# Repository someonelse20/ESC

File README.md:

# ESC

A custom designed electronic speed controller that supports up to 7 cell LiPo batteries with 30 amps (untested).
I made this as part of my overall project of making a drone from scratch.

## Pinout

| Pin # | Function  |
| ----- | --------- |
| 1     | PWM IN    |
| 2     | Direction |
| 3     | GND       |

Pull the Direction pin low (default) for clockwise rotation or high (3.3v) for counter clockwise rotation.
Alternatively, leave the solder bridge on the bottom of the board open for clockwise and closed for counter clockwise.

## PCB Layout

## Schematic

## BOM

| Name         | Purpose                   | Quantity | Total Cost (USD) | Link                          | Distributor |
| ------------ | ------------------------- | -------- | ---------------- | ----------------------------- | ----------- |
| PCB          | 	The Circuit Board        | 5        | 7.00             | [JLCPCB](https://jlcpcb.com/) | JLCPCB      |
| PCB Assembly | Assembly for the board    | 2        | 78.46            | [JLCPCB](https://jlcpcb.com/) | JLCPCB      |

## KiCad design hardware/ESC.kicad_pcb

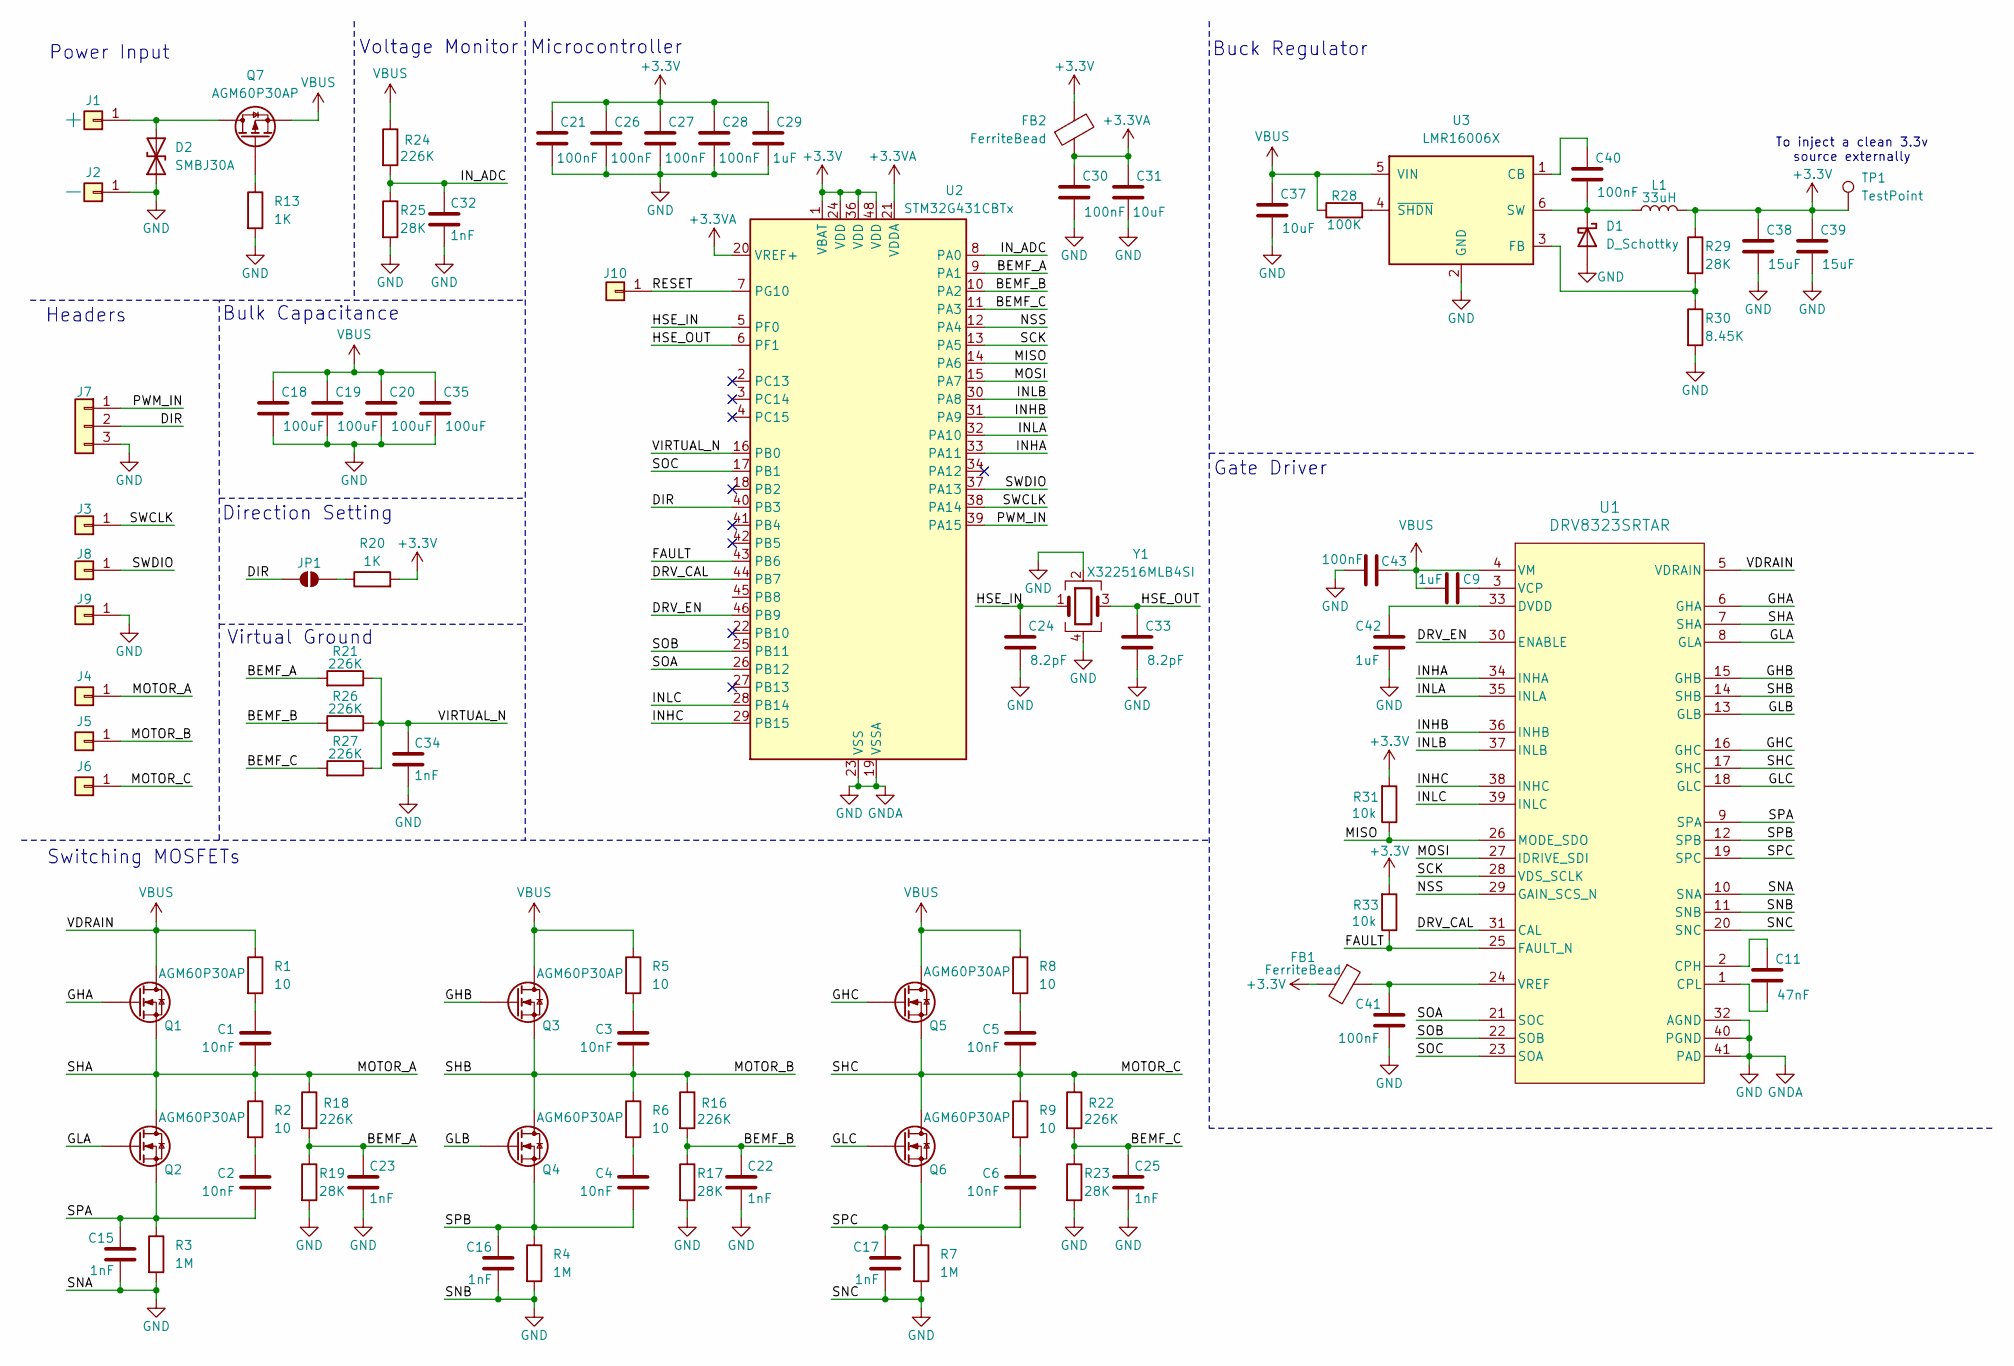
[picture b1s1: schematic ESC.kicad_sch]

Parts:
C1, C2, C3, C4, C5, C6: 10nF; C_0402_1005Metric
C9, C42: 1uF; C_0402_1005Metric
C11: 47nF; C_0402_1005Metric
C15, C16, C17, C22, C23, C25, C32, C34: 1nF; C_0402_1005Metric
C18, C19, C20, C35: 100uF; C_Elec_6.3x7.7
C21, C26, C27, C28, C30, C40, C41, C43: 100nF; C_0402_1005Metric
C24, C33: 8.2pF; C_0402_1005Metric
C29: 1uF; C_0603_1608Metric
C31: 10uF; C_0402_1005Metric
C37: 10uF; C_0603_1608Metric
C38, C39: 15uF; C_0603_1608Metric
D1: D_Schottky; D_SOD-123
D2: SMBJ30A; D_SMA
FB1, FB2: FerriteBead; L_0603_1608Metric
J1, J4, J5, J6: +; SolderWire-4sqmm_1x01_D3mm_OD6mm
J2: -; SolderWire-4sqmm_1x01_D3mm_OD6mm
J3, J8, J9, J10: +; SolderWirePad_1x01_SMD_2x4mm
J7: Conn_01x03; PinHeader_1x03_P2.54mm_Vertical
JP1: SolderJumper_2_Open; SolderJumper-2_P1.3mm_Open_RoundedPad1.0x1.5mm
L1: 33uH; L_APV_ANR4030
Q1, Q2, Q3, Q4, Q5, Q6, Q7: AGM60P30AP; D_QFN_3.3x3.3mm_P0.65mm
R1, R2, R5, R6, R8, R9: 10; R_0603_1608Metric
R3, R4, R7: 1M; R_1206_3216Metric
R13: 1K; R_0603_1608Metric
R16, R18, R21, R22, R24, R26, R27: 226K; R_0402_1005Metric
R17, R19, R23, R25, R29: 28K; R_0402_1005Metric
R20: 1K; R_0402_1005Metric
R28: 100K; R_0402_1005Metric
R30: 8.45K; R_0402_1005Metric
R31, R33: 10k; R_0402_1005Metric
TP1: TestPoint; TestPoint_Pad_1.5x1.5mm
U1: DRV8323SRTAR
U2: STM32G431CBTx; LQFP-48_7x7mm_P0.5mm
U3: LMR16006X; SOT-23-6
Y1: X322516MLB4SI; Crystal_SMD_3225-4Pin_3.2x2.5mm

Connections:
+3.3V: C21.1, C26.1, C27.1, C28.1, C29.1, C38.1, C39.1, FB1.2, FB2.2, L1.2, R20.2, R29.1, R31.2, R33.2, TP1.1 (1_1), U2.1 (VBAT), U2.24 (VDD), U2.36 (VDD), U2.48 (VDD)
+3.3VA: C30.1, C31.1, FB2.1, U2.20 (VREF+), U2.21 (VDDA)
/BEMF_A: C23.1, R18.2, R19.1, R21.2, U2.9 (PA1)
/BEMF_B: C22.1, R16.2, R17.1, R26.2, U2.10 (PA2)
/BEMF_C: C25.1, R22.2, R23.1, R27.2, U2.11 (PA3)
/DIR: J7.2, JP1.1 (A), U2.40 (PB3)
/DRV_CAL: U1.31 (CAL), U2.44 (PB7)
/DRV_EN: U1.30 (ENABLE), U2.46 (PB9)
/FAULT: R33.1, U1.25 (FAULT_N), U2.43 (PB6)
/GHA: Q1.2 (G), U1.6 (GHA)
/GHB: Q3.2 (G), U1.15 (GHB)
/GHC: Q5.2 (G), U1.16 (GHC)
/GLA: Q2.2 (G), U1.8 (GLA)
/GLB: Q4.2 (G), U1.13 (GLB)
/GLC: Q6.2 (G), U1.18 (GLC)
/HSE_IN: C24.1, U2.5 (PF0), Y1.1
/HSE_OUT: C33.1, U2.6 (PF1), Y1.3
/INHA: U1.34 (INHA), U2.33 (PA11)
/INHB: U1.36 (INHB), U2.31 (PA9)
/INHC: U1.38 (INHC), U2.29 (PB15)
/INLA: U1.35 (INLA), U2.32 (PA10)
/INLB: U1.37 (INLB), U2.30 (PA8)
/INLC: U1.39 (INLC), U2.28 (PB14)
/IN_ADC: C32.1, R24.2, R25.1, U2.8 (PA0)
/MISO: R31.1, U1.26 (MODE_SDO), U2.14 (PA6)
/MOSI: U1.27 (IDRIVE_SDI), U2.15 (PA7)
/MOTOR_A: C1.2, J4.1 (Pin_1_1), Q1.1 (S), Q2.3 (D), R2.1, R18.1, U1.7 (SHA)
/MOTOR_B: C3.2, J5.1 (Pin_1_1), Q3.1 (S), Q4.3 (D), R6.1, R16.1, U1.14 (SHB)
/MOTOR_C: C5.2, J6.1 (Pin_1_1), Q5.1 (S), Q6.3 (D), R9.1, R22.1, U1.17 (SHC)
/NSS: U1.29 (GAIN_SCS_N), U2.12 (PA4)
/PWM_IN: J7.1, U2.39 (PA15)
/RESET: J10.1 (Pin_1_1), U2.7 (PG10)
/SCK: U1.28 (VDS_SCLK), U2.13 (PA5)
/SOA: U1.21 (SOC), U2.26 (PB12)
/SOB: U1.22 (SOB), U2.25 (PB11)
/SOC: U1.23 (SOA), U2.17 (PB1)
/SPA: C2.2, C15.1, Q2.1 (S), R3.1, U1.9 (SPA)
/SPB: C4.2, C16.1, Q4.1 (S), R4.1, U1.12 (SPB)
/SPC: C6.2, C17.1, Q6.1 (S), R7.1, U1.19 (SPC)
/SWCLK: J3.1 (Pin_1_1), U2.38 (PA14)
/SWDIO: J8.1 (Pin_1_1), U2.37 (PA13)
/VIRTUAL_N: C34.1, R21.1, R26.1, R27.1, U2.16 (PB0)
GND: C15.2, C16.2, C17.2, C18.2, C19.2, C20.2, C21.2, C22.2, C23.2, C24.2, C25.2, C26.2, C27.2, C28.2, C29.2, C30.2, C31.2, C32.2, C33.2, C34.2, C35.2, C37.2, C38.2, C39.2, C41.2, C42.2, C43.2, D1.2 (A), D2.1 (A1), J2.1 (Pin_1_1), J7.3, J9.1 (Pin_1_1), R3.2, R4.2, R7.2, R13.2, R17.2, R19.2, R23.2, R25.2, R30.2, U1.10 (SNA), U1.11 (SNB), U1.20 (SNC), U1.32 (AGND), U1.40 (PGND), U1.41 (PAD), U2.19 (VSSA), U2.23 (VSS), U2.35 (VSS), U2.47 (VSS), U3.2 (GND), Y1.2, Y1.4
unnamed: C1.1, R1.2
unnamed: C2.1, R2.2
unnamed: C3.1, R5.2
unnamed: C4.1, R6.2
unnamed: C5.1, R8.2
unnamed: C6.1, R9.2
unnamed: C40.2, D1.1 (K), L1.1, U3.6 (SW)
unnamed: D2.2 (A2), J1.1 (Pin_1_1), Q7.3 (D)
unnamed: JP1.2 (B), R20.1
unnamed: Q7.2 (G), R13.1
unnamed: C11.1, U1.2 (CPH)
unnamed: C11.2, U1.1 (CPL)
unnamed: C42.1, U1.33 (DVDD)
unnamed: C9.2, U1.3 (VCP)
unnamed: C41.1, FB1.1, U1.24 (VREF)
unnamed: C40.1, U3.1 (CB)
unnamed: R29.2, R30.1, U3.3 (FB)
unnamed: R28.2, U3.4 (~SHDN)
VBUS: C9.1, C18.1, C19.1, C20.1, C35.1, C37.1, C43.1, Q1.3 (D), Q3.3 (D), Q5.3 (D), Q7.1 (S), R1.1, R5.1, R8.1, R24.1, R28.1, U1.4 (VM), U1.5 (VDRAIN), U3.5 (VIN)

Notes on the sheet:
Buck Regulator
Bulk Capacitance
Switching MOSFETs
To inject a clean 3.3v source externally
Power Input
Microcontroller
Direction Setting
Virtual Ground
Voltage Monitor
Gate Driver
Headers

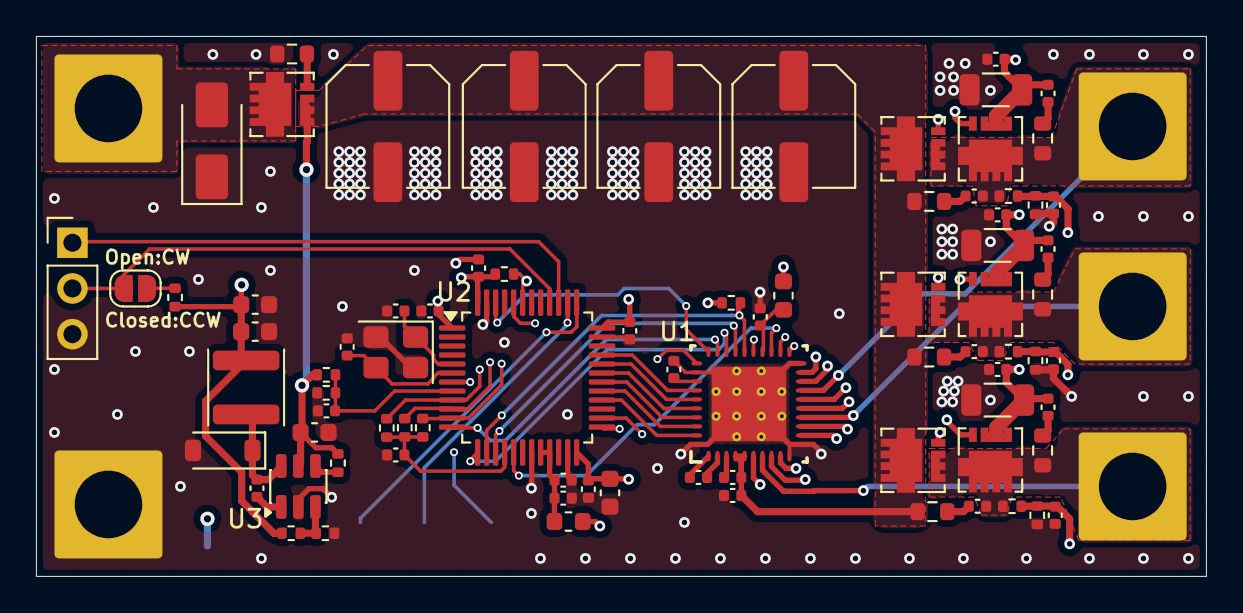
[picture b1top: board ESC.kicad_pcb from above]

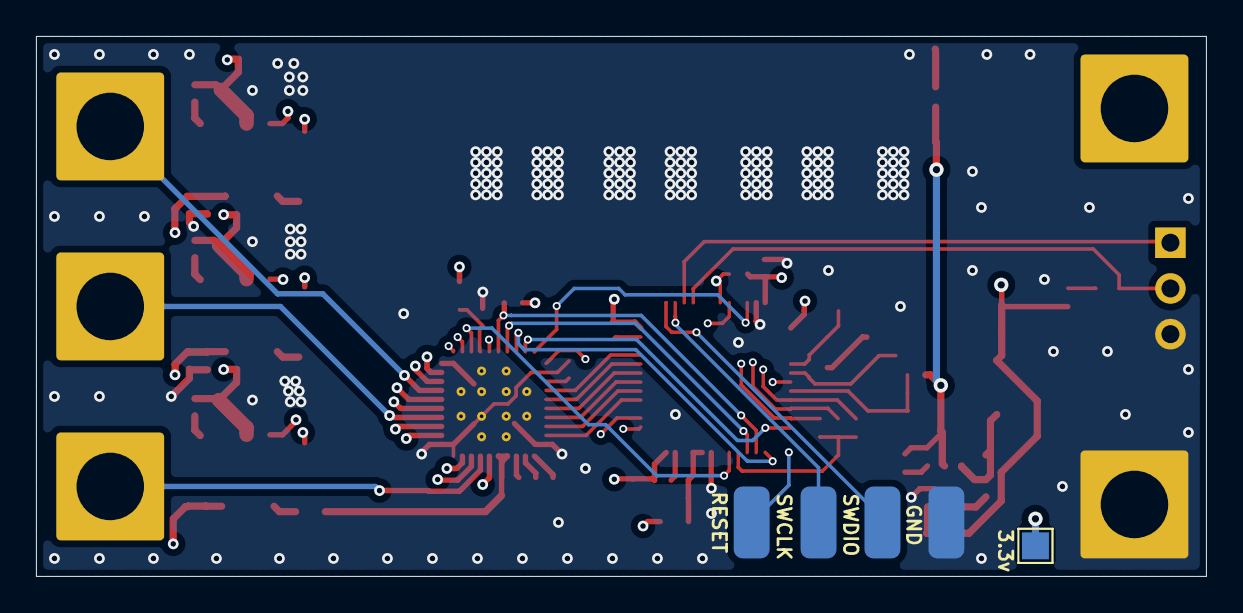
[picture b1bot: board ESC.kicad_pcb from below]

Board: 4 copper layers, 65.0 x 30.0 mm, 91 parts (5 on the bottom side), 62 nets.

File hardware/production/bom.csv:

Designator,Footprint,Quantity,Value,LCSC Part #
"C1, C2, C3, C4, C5, C6",0402,6,10nF,
"C10, C21, C26, C27, C28, C30, C7, C9",0402,8,100nF,
C11,0402,1,47nF,
"C12, C13",0402,2,1uF,
C14,0603,1,2.2uF,
"C15, C16, C17, C22, C23, C25, C32, C34",0402,8,1nF,
"C18, C19, C20",C_Elec_6.3x7.7,3,100uF,
"C24, C33",0402,2,8.2pF,
C29,0603,1,1uF,
C31,0402,1,10uF,
C8,0603,1,10uF,
D1,D_SOD-123,1,D_Schottky,
D2,D_SMA,1,SMBJ30A,
"FB1, FB2",0603,2,FerriteBead,
"J1, J4, J5, J6",SolderWire-4sqmm_1x01_D3mm_OD6mm,4,+,
"J10, J3, J8, J9",SolderWirePad_1x01_SMD_2x4mm,4,+,
J2,SolderWire-4sqmm_1x01_D3mm_OD6mm,1,-,
J7,PinHeader_1x03_P2.54mm_Vertical,1,Conn_01x03,
L1,L_APV_ANR6020,1,22uH,
"Q1, Q2, Q3, Q4, Q5, Q6",PQFN-8-EP_6x5mm_P1.27mm_Generic,6,AGM60P30AP,
Q7,PQFN-8-EP_6x5mm_P1.27mm_Generic,1,AGM60P30A,
"R1, R2, R5, R6, R8, R9",0603,6,10,
R10,0402,1,100K,
R11,0402,1,3.3K,
"R12, R20",0402,2,1K,
R13,0603,1,1K,
"R14, R15, R28",0402,3,10k,
"R16, R18, R21, R22, R24, R26, R27",0402,7,162K,
"R17, R19, R23, R25",0402,4,20K,
"R3, R4, R7",1206,3,1M,
SW3,SW_Push_SPST_NO_Alps_SKRK,1,SW_Push,
U1,QFN-48-1EP_7x7mm_P0.5mm_EP5.1x5.1mm_ThermalVias,1,DRV8323RSRGZR,
U2,LQFP-48_7x7mm_P0.5mm,1,STM32G431CBTx,
Y1,Crystal_SMD_3225-4Pin_3.2x2.5mm,1,X322516MLB4SI,

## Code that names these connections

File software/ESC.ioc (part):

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Mcu.Name=STM32G431C(6-8-B)Tx
Mcu.Package=LQFP48
Mcu.UserName=STM32G431CBTx
PA0.Mode=IN1-Single-Ended
PA0.Signal=ADC1_IN1
PA1.Mode=IN2-Single-Ended
PA1.Signal=ADC1_IN2
PA10.Signal=S_TIM1_CH3
PA11.Signal=S_TIM1_CH4
PA13.Signal=SYS_JTMS-SWDIO
PA14.Signal=SYS_JTCK-SWCLK
PA15.Signal=S_TIM2_CH1
PA2.Mode=IN3-Single-Ended
PA2.Signal=ADC1_IN3
PA3.Mode=IN4-Single-Ended
PA3.Signal=ADC1_IN4
PA4.Mode=NSS_Signal_Hard_Output
PA4.Signal=SPI1_NSS
PA5.Mode=Full_Duplex_Master
PA5.Signal=SPI1_SCK
PA6.Mode=Full_Duplex_Master
PA6.Signal=SPI1_MISO
PA7.Mode=Full_Duplex_Master
PA7.Signal=SPI1_MOSI
PA8.Signal=S_TIM1_CH1
PA9.Signal=S_TIM1_CH2
PB0.Mode=IN15-Single-Ended
PB0.Signal=ADC1_IN15
PB1.Mode=IN12-Single-Ended
PB1.Signal=ADC1_IN12
PB11.Mode=IN14-Single-Ended
PB11.Signal=ADC1_IN14
PB12.Mode=IN11-Single-Ended
PB12.Signal=ADC1_IN11
PB14.Signal=S_TIM15_CH1
PB15.Signal=S_TIM15_CH2
PB3.GPIOParameters=GPIO_PuPd
PB3.GPIO_PuPd=GPIO_PULLDOWN
PB3.Signal=GPIO_Input
PB6.Signal=GPIO_Output
PB7.GPIOParameters=GPIO_PuPd
PB7.GPIO_PuPd=GPIO_PULLDOWN
PB7.Signal=GPIO_Output
PB9.GPIOParameters=GPIO_PuPd
PB9.GPIO_PuPd=GPIO_PULLUP
PB9.Signal=GPIO_Output
PF0-OSC_IN.Mode=HSE-External-Oscillator
PF0-OSC_IN.Signal=RCC_OSC_IN
PF1-OSC_OUT.Mode=HSE-External-Oscillator
PF1-OSC_OUT.Signal=RCC_OSC_OUT
RCC.HSE_VALUE=16000000
RCC.SYSCLKFreq_VALUE=64000000
RCC.SYSCLKSource=RCC_SYSCLKSOURCE_PLLCLK
board=custom

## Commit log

2026-03-19 added project files
2026-03-19 started schematic
2026-03-23 finished most of schematic
2026-03-23 layout first draft
2026-03-23 started routing schematic
2026-03-24 routing pcb
2026-03-24 updated to kicad 10.0
2026-03-24 moved regulator
2026-03-24 finished pcb
2026-03-24 generated code
2026-03-25 added boot button and reset pad
2026-03-26 added filter cap to virtual gnd
2026-03-27 wrote firmware outline
2026-03-30 updated hardware
2026-03-31 wrote more firmware
2026-03-31 increase via and trace size
2026-04-01 wrote firmware
2026-04-02 changed inductor size
2026-04-04 beautified schematic
2026-04-04 added assets
2026-04-04 updated silkscreen
2026-04-04 updated production files
2026-04-04 added step file
2026-04-04 added journal
2026-05-07 added new single side design
2026-05-08 added new regulator and gate driver
2026-05-08 added lables
2026-05-08 added lables but right this time
2026-05-08 fixed regulator cap value
2026-05-11 updated pcb
2026-05-11 made pcb layout
2026-05-11 added bulk capacitor
2026-05-15 routed pcb
2026-05-17 touched up pcb
2026-05-20 updated assest pictures
2026-05-20 fixed assets
